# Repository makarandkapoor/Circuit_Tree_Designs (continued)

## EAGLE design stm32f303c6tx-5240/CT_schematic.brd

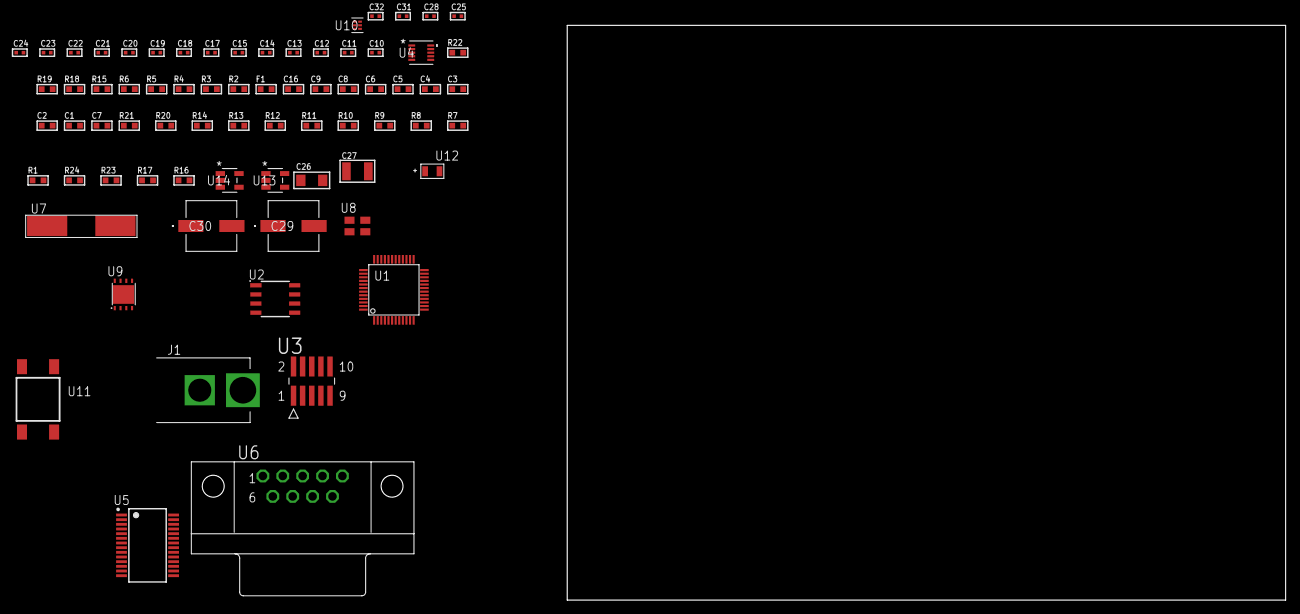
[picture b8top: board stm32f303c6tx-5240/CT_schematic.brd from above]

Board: 2 copper layers, 100.0 x 80.0 mm, 72 parts (0 on the bottom side), 49 nets, no tracks yet.

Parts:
C1, C9, C16: 1e-06; C0603
C2, C3, C4, C5, C6: 1e-07; C0603
C7: 4.7e-06; C0603
C8: 1e-08; C0603
C10, C11: 1e-11; C0402
C12, C24, C25, C31, C32: 1e-08; C0402
C13, C14, C15, C17, C18, C19, C20, C21, C22, C23, C28: 1e-07; C0402
C26: 1e-05; C1206
C27: 1e-05; C1210
C29, C30: 0.0001; EXV-9H
F1: 240.0; L0603
J1: PJ-037B; PJ-037B_PACKAGE
R1, R7, R8, R9, R10, R11, R12, R13, R14, R20, R21: 10000.0; R0603
R2, R19: 1000.0; R0603
R3: 1600.5; R0603
R4: 4700.0; R0603
R5, R6: 2200.0; R0603
R15: 5.0; R0603
R16, R17: 100000.0; R0603
R18: 2231.0; R0603
R22: 9100.0; R0603
R23: 680000.0; R0603
R24: 120000.0; R0603
U1: STM32F303C6T6; LQFP48
U2: AT25640B-SSHL-T; SOIC-8
U3: FTSH-105-01-L-DV-K; SAMTEC_FTSH-105-01-L-DV-K
U4: MAG3110FCR1; DFN-10
U5: ST3241EBPR; SSOP-28
U6: 182-009-113R531; 182-009-MALE
U7: ABLS-25.000MHZ-B2F-T
U8: ASEK-32.768KHz-ECST; ASEK
U9: LP3878SDX-ADJ/NOPB; WSON-8
U10: TPS3895ADRYR; SON-6
U11: 4-1437565-2; SW_4-1437565-2
U12: Q65110A2395; LGM67K-G1J2-24-Z
U13, U14: nc7sz125m5x; NC7SZ125M5X

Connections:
CLK_CRYSTAL_U1_5: C10.1, U1.5, U7.1
CLK_CRYSTAL_U1_6: C11.1, U1.6, U7.2
CLK_U1_3: U1.3, U8.3
GND: C1.2, C2.2, C3.2, C4.2, C5.2, C6.2, C7.2, C8.2, C9.2, C10.2, C11.2, C12.2, C13.2, C14.2, C15.2, C16.2, C17.2, C18.2, C19.2, C22.2, C23.2, C24.2, C25.2, C26.2, C27.2, C28.2, C29.2, C30.2, C31.2, C32.2, J1.2, R2.2, R7.2, R14.2, R15.2, R19.2, R22.2, R24.2, U1.8, U1.23, U1.35, U1.47, U2.4, U3.3, U3.5, U4.5, U4.10, U5.23, U5.25, U6.5, U8.2, U9.3, U9.PAD, U10.2, U12.C, U13.2, U13.3, U14.1, U14.3
NET_U1_7: R4.1, U1.7, U14.4
NET_U1_9: C8.1, C9.1, F1.1, U1.9
NET_U1_42: R5.1, U1.42, U4.7
NET_U1_43: R6.1, U1.43, U4.6
NET_U1_44: R7.1, U1.44
NET_U1_45: R3.1, U1.45, U12.A
NET_U1_46: R1.1, U1.46, U11.3, U11.4
NET_U2_3: R8.1, U2.3
NET_U2_7: R10.1, U2.7
NET_U3_9: R15.1, U3.9
NET_U4_1: C14.1, U4.1
NET_U4_4: C17.1, U4.4
NET_U5_1: C21.1, U5.1
NET_U5_2: C21.2, U5.2
NET_U5_3: C23.1, U5.3
NET_U5_22: R16.1, U5.22
NET_U5_24: C20.2, U5.24
NET_U5_27: C22.1, U5.27
NET_U5_28: C20.1, U5.28
NET_U6_2: U5.4, U6.2
NET_U6_3: U5.9, U6.3
NET_U6_7: U5.5, U6.7
NET_U6_8: U5.10, U6.8
NET_U9_1: C25.1, U9.1
NET_U9_6: R18.2, R19.1, U9.6
NET_U9_8: R17.1, U9.8
NET_U10_1: R21.1, R22.1, U10.1
NET_U10_3: R23.2, R24.1, U10.3
NET_U10_4: R20.1, U10.4, U13.4, U14.2
NET_U11_1: R2.1, U11.1, U11.2
PROC_SPI1_MISO: U1.16, U2.2
PROC_SPI1_MOSI: U1.17, U2.5
PROC_SPI1_NSS: R9.1, U1.14, U2.1
PROC_SPI1_SCK: U1.15, U2.6
PROC_SYS_JTCK_SWCLK: R14.1, U1.37, U3.4
PROC_SYS_JTDI: R12.1, U1.38, U3.8
PROC_SYS_JTDO_TRACESWO: U1.39, U3.6
PROC_SYS_JTMS_SWDIO: R13.1, U1.34, U3.2
PROC_USART1_CTS: U1.32, U5.13
PROC_USART1_RTS: U1.33, U5.18
PROC_USART1_RX: U1.31, U5.19
PROC_USART1_TX: U1.30, U5.14
RST_OUT_U3_JTAG_RST_B: R11.1, U3.10, U13.1
VCC_S1_6V6: C26.1, C29.1, C30.1, J1.1, R17.2, U9.4
VCC_TIER1_3V3: C1.1, C2.1, C3.1, C4.1, C5.1, C6.1, C7.1, C12.1, C13.1, C15.1, C16.1, C18.1, C19.1, C24.1, C27.1, C28.1, C31.1, C32.1, F1.2, R1.2, R3.2, R4.2, R5.2, R6.2, R8.2, R9.2, R10.2, R11.2, R12.2, R13.2, R16.2, R18.1, R20.2, R21.2, R23.1, U1.1, U1.24, U1.36, U1.48, U2.8, U3.1, U4.2, U4.8, U5.26, U8.4, U9.5, U10.6, U13.5, U14.5
